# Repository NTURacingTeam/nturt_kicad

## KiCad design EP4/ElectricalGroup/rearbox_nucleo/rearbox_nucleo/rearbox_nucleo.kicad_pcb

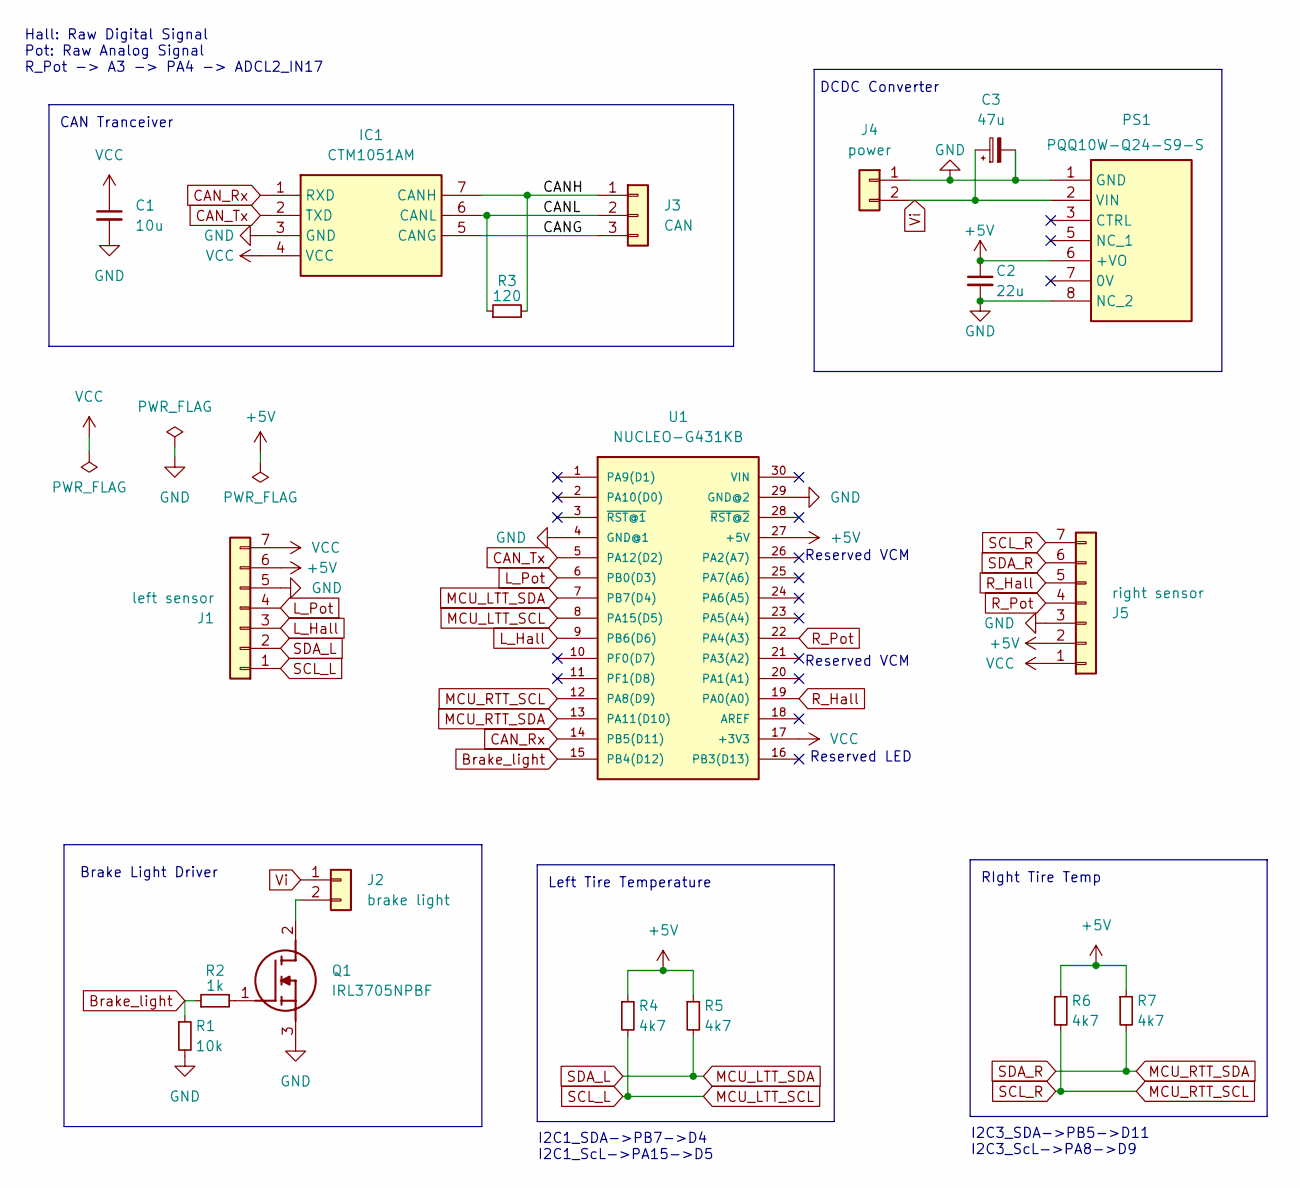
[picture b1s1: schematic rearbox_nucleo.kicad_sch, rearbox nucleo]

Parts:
C1: 10u; C_0805_2012Metric_Pad1.18x1.45mm_HandSolder
C2: 22u; CP_Radial_D6.3mm_P2.50mm
C3: 47u; CP_Radial_Tantal_D6.0mm_P2.50mm
IC1: CTM1051AM; Manufacturer_Part_Number CTM1051AM
J1: left sensor; JST_XH_B7B-XH-A_1x07_P2.50mm_Vertical
J2: brake light; JST_XH_B2B-XH-A_1x02_P2.50mm_Vertical
J3: CAN; JST_XH_B3B-XH-A_1x03_P2.50mm_Vertical
J4: power; JST_XH_B2B-XH-A_1x02_P2.50mm_Vertical
J5: right sensor; JST_XH_B7B-XH-A_1x07_P2.50mm_Vertical
PS1: PQQ10W-Q24-S9-S; PQQ10WQ24S9S; Manufacturer_Part_Number PQQ10W-Q24-S9-S
Q1: IRL3705NPBF; TO254P469X1042X1930-3P; Manufacturer_Part_Number IRL3705NPBF; Mouser Part Number 942-IRL3705NPBF
R1: 10k; R_0603_1608Metric_Pad0.98x0.95mm_HandSolder
R2: 1k; R_0603_1608Metric_Pad0.98x0.95mm_HandSolder
R3: 120; R_1206_3216Metric_Pad1.30x1.75mm_HandSolder
R4, R5, R6, R7: 4k7; R_0603_1608Metric_Pad0.98x0.95mm_HandSolder
U1: NUCLEO-G431KB; MANUFACTURER_PART_NUMBER NUCLEO-F303K8

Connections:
+5V: C2.1, J1.6, J5.2, PS1.6 (+VO), R4.1, R5.1, R6.1, R7.1, U1.27 (+5V)
/CANG: IC1.5 (CANG), J3.3
/CANH: IC1.7 (CANH), J3.1, R3.2
/CANL: IC1.6 (CANL), J3.2, R3.1
Brake_light: R1.1, R2.1, U1.15 (PB4(D12))
CAN_Rx: IC1.1 (RXD), U1.14 (PB5(D11))
CAN_Tx: IC1.2 (TXD), U1.5 (PA12(D2))
GND: C1.2, C2.2, C3.2, IC1.3 (GND), J1.5, J4.1, J5.3, PS1.1 (GND), PS1.8 (NC_2), Q1.3 (S), R1.2, U1.4 (GND@1), U1.29 (GND@2)
L_Hall: J1.3, U1.9 (PB6(D6))
L_Pot: J1.4, U1.6 (PB0(D3))
MCU_LTT_SCL: J1.1, R4.2, U1.8 (PA15(D5))
MCU_LTT_SDA: J1.2, R5.2, U1.7 (PB7(D4))
MCU_RTT_SCL: J5.7, R6.2, U1.12 (PA8(D9))
MCU_RTT_SDA: J5.6, R7.2, U1.13 (PA11(D10))
unnamed: J2.2, Q1.2 (D)
unnamed: Q1.1 (G), R2.2
R_Hall: J5.5, U1.19 (PA0(A0))
R_Pot: J5.4, U1.22 (PA4(A3))
VCC: C1.1, IC1.4 (VCC), J1.7, J5.1, U1.17 (+3V3)
Vi: C3.1, J2.1, J4.2, PS1.2 (VIN)

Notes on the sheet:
RIght Tire Temp
Brake Light Driver
I2C3_SDA->PB5->D11 I2C3_ScL->PA8->D9
Reserved VCM
Reserved LED
Left Tire Temperature
I2C1_SDA->PB7->D4 I2C1_ScL->PA15->D5
CAN Tranceiver
Hall: Raw Digital Signal Pot: Raw Analog Signal R_Pot -> A3 -> PA4 -> ADCL2_IN17
DCDC Converter

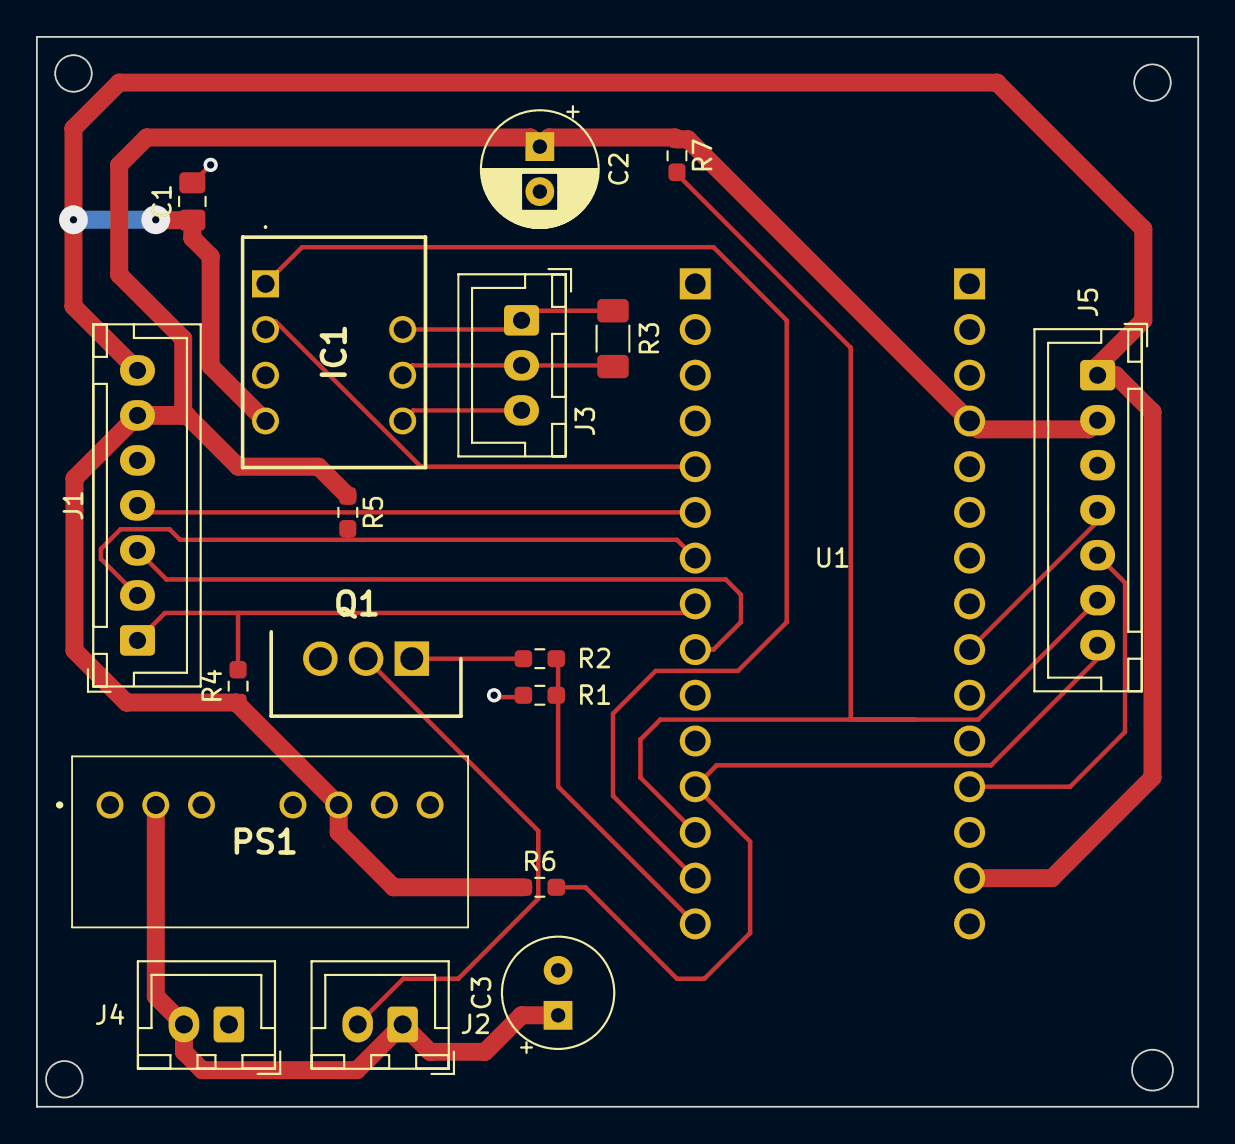
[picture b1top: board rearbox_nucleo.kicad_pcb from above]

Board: 2 copper layers, 64.5 x 59.4 mm, 19 parts (0 on the bottom side), 20 nets.

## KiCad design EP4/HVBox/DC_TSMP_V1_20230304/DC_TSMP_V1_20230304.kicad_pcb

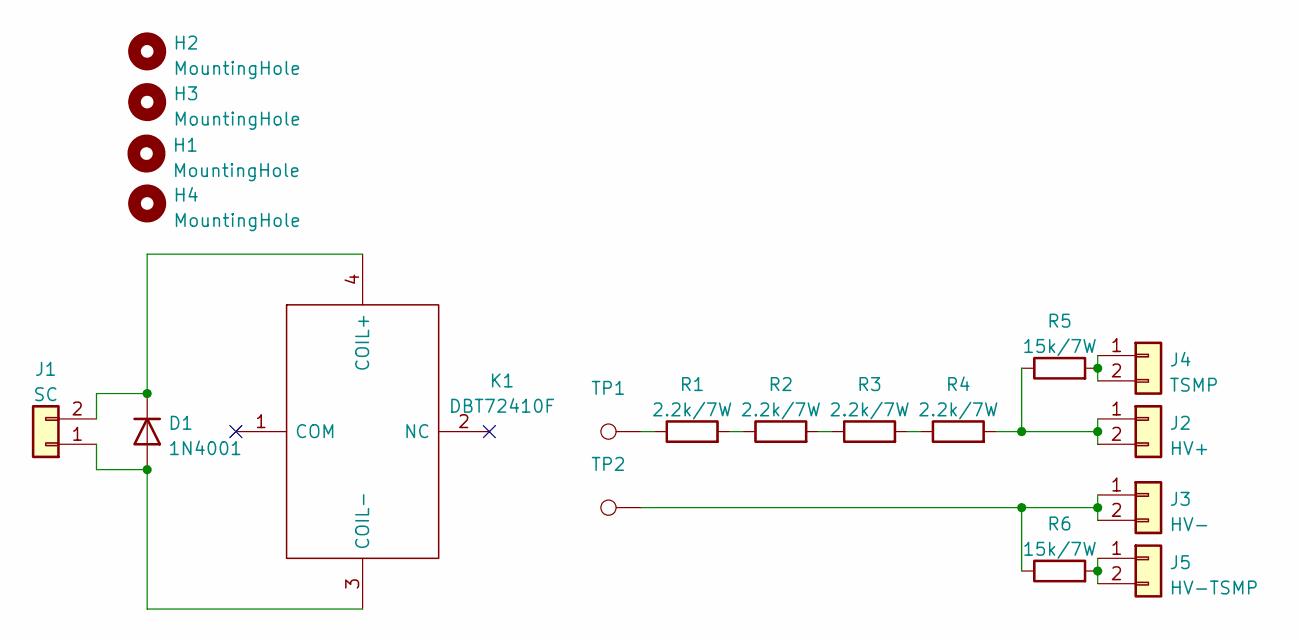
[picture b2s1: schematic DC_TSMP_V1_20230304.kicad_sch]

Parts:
D1: 1N4001; D_DO-41_SOD81_P10.16mm_Horizontal
H1, H2, H3, H4: MountingHole; MountingHole_4.3mm_M4
J1: SC; JST_PH_B2B-PH-K_1x02_P2.00mm_Vertical
J2: HV+; DF33C2P33DSA24
J3: HV-; DF33C2P33DSA24
J4: TSMP; DF33C2P33DSA24
J5: HV-TSMP; DF33C2P33DSA24
K1: DBT72410F; DBT72410; Manufacturer_Part_Number DBT72410
R1, R2, R3, R4: 2.2k/7W; RESM24595X990N
R5, R6: 15k/7W; RESM24595X990N
TP1, TP2: TestPoint_Loop_D2.50mm_Drill1.0mm

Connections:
unnamed: D1.1 (K), J1.2, K1.4 (COIL+)
unnamed: D1.2 (A), J1.1, K1.3 (COIL-)
unnamed: J2.1, J2.2, R4.2, R5.1
unnamed: J3.1, J3.2, R6.1, TP2.1
unnamed: J4.1, J4.2, R5.2
unnamed: J5.1, J5.2, R6.2
unnamed: R1.1, TP1.1
unnamed: R1.2, R2.1
unnamed: R2.2, R3.1
unnamed: R3.2, R4.1

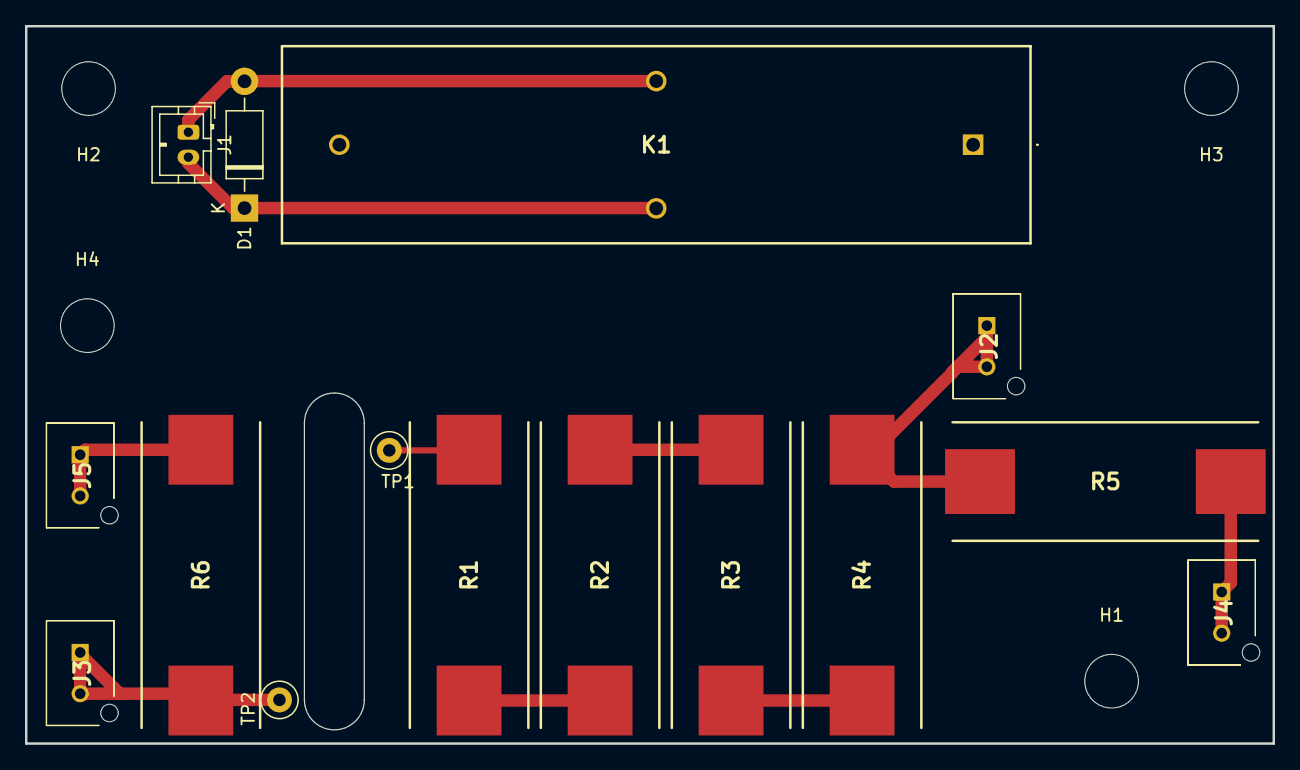
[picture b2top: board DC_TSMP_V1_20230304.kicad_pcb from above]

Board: 2 copper layers, 100.0 x 57.5 mm, 19 parts (0 on the bottom side), 10 nets.

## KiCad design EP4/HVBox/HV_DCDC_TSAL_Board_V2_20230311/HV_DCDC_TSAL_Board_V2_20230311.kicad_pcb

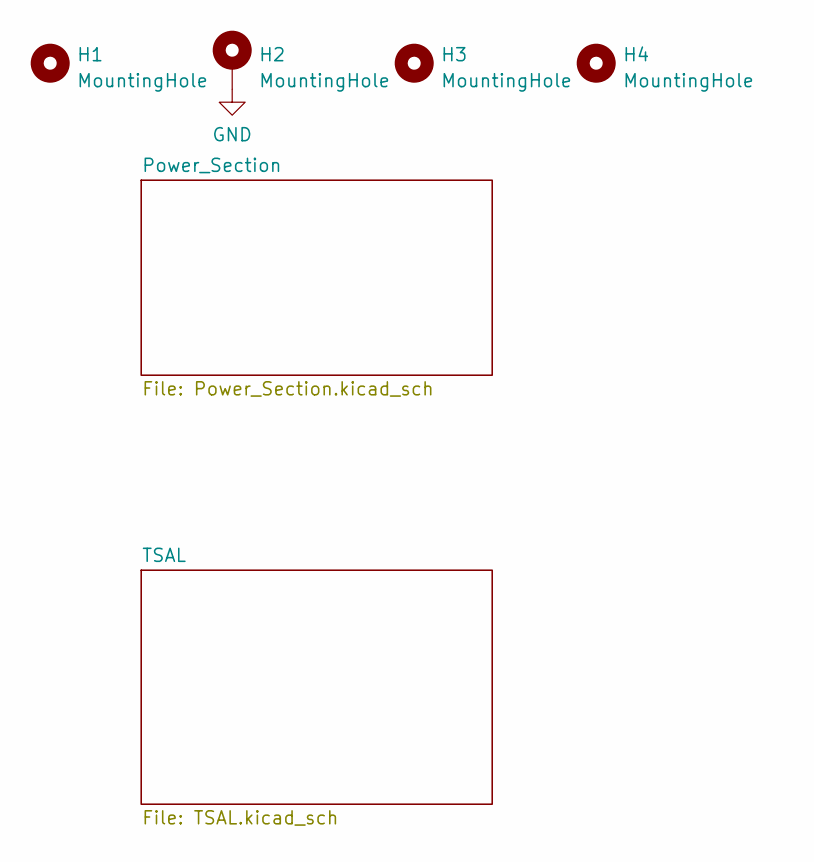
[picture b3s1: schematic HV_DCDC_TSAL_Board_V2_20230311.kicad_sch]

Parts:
H1, H3, H4: MountingHole; MountingHole_4.3mm_M4
H2: MountingHole; MountingHole_4.3mm_M4_Pad_Via

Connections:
GND: H2.1; also elsewhere on the board

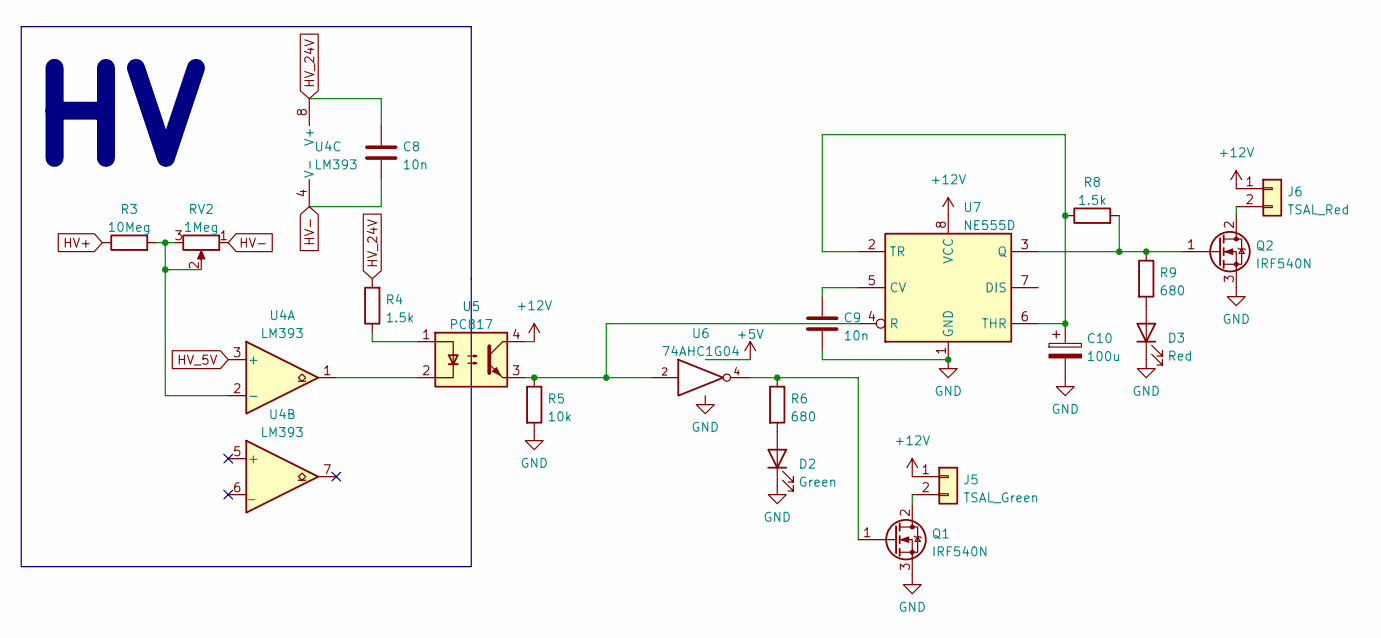
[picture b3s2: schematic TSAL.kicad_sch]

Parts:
C8: 10n; C_Disc_D4.7mm_W2.5mm_P5.00mm
C9: 10n; C_1206_3216Metric_Pad1.33x1.80mm_HandSolder
C10: 100u; C_1206_3216Metric_Pad1.33x1.80mm_HandSolder
D2: Green; D_1206_3216Metric_Pad1.42x1.75mm_HandSolder
D3: Red; D_1206_3216Metric_Pad1.42x1.75mm_HandSolder
J5: TSAL_Green; JST_PH_B2B-PH-K_1x02_P2.00mm_Vertical
J6: TSAL_Red; JST_PH_B2B-PH-K_1x02_P2.00mm_Vertical
Q1, Q2: IRF540N; TO-220-3_Vertical
R3: 10Meg; R_Axial_DIN0309_L9.0mm_D3.2mm_P15.24mm_Horizontal
R4: 1.5k; R_Axial_DIN0309_L9.0mm_D3.2mm_P12.70mm_Horizontal
R5: 10k; R_1206_3216Metric_Pad1.30x1.75mm_HandSolder
R6, R9: 680; R_1206_3216Metric_Pad1.30x1.75mm_HandSolder
R8: 1.5k; R_1206_3216Metric_Pad1.30x1.75mm_HandSolder
RV2: 1Meg; Potentiometer_Vishay_T73YP_Vertical
U4: LM393; DIP-8_W10.16mm
U5: PC817; DIP-4_W7.62mm
U6: 74AHC1G04; SOT-353_SC-70-5_Handsoldering
U7: NE555D; SOIC-8_3.9x4.9mm_P1.27mm

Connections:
+5V: U6.5 (VCC); also elsewhere on the board
+12V: J5.1, J6.1, U5.4, U7.8 (VCC); also elsewhere on the board
GND: C9.2, C10.2, D2.1 (K), D3.1 (K), Q1.3 (S), Q2.3 (S), R5.2, U6.3 (GND), U7.1 (GND); also elsewhere on the board
HV+: R3.1; also elsewhere on the board
HV-: C8.2, RV2.1, U4.4 (V-); also elsewhere on the board
HV_5V: U4.3 (+); also elsewhere on the board
HV_24V: C8.1, R4.2, U4.8 (V+); also elsewhere on the board
unnamed: C9.1, U7.5 (CV)
unnamed: C10.1, R8.1, U7.2 (TR), U7.6 (THR)
unnamed: D2.2 (A), R6.2
unnamed: D3.2 (A), R9.2
unnamed: J5.2, Q1.2 (D)
unnamed: J6.2, Q2.2 (D)
unnamed: Q1.1 (G), R6.1, U6.4
unnamed: Q2.1 (G), R8.2, R9.1, U7.3 (Q)
unnamed: R3.2, RV2.2, RV2.3, U4.2 (-)
unnamed: R4.1, U5.1
unnamed: R5.1, U5.3, U6.2, U7.4 (R)
unnamed: U4.1, U5.2

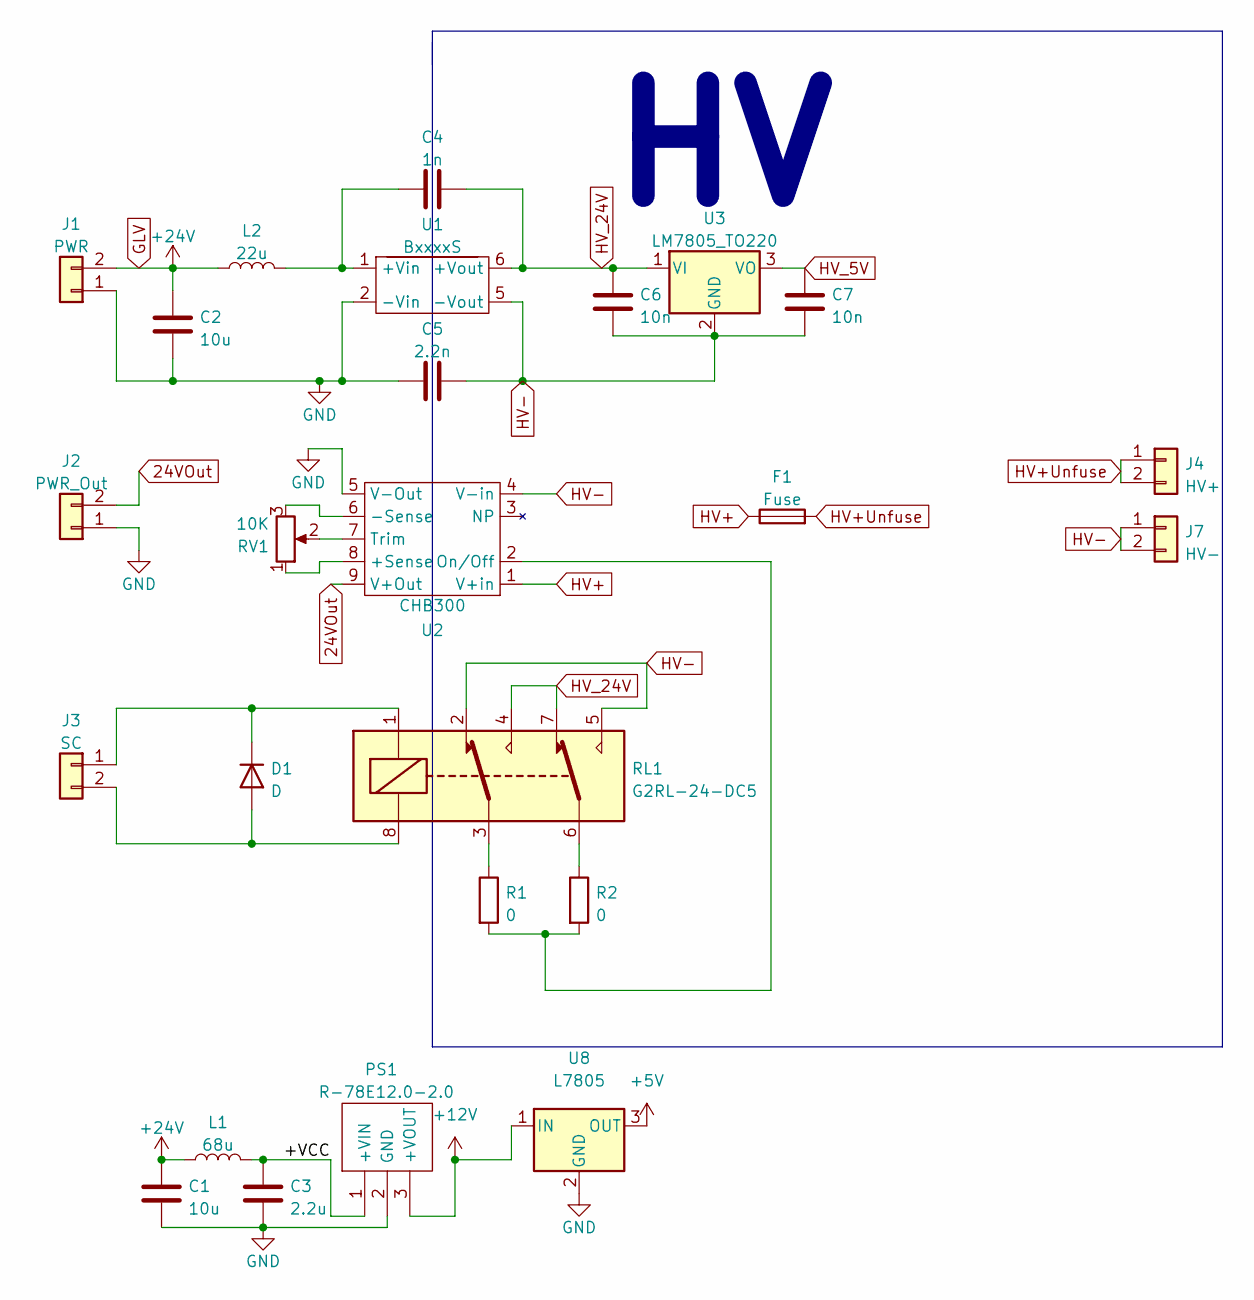
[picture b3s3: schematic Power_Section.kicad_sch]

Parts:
C1, C2: 10u; C_1206_3216Metric_Pad1.33x1.80mm_HandSolder
C3: 2.2u; C_1206_3216Metric_Pad1.33x1.80mm_HandSolder
C4: 1n; C_Axial_L5.1mm_D3.1mm_P15.00mm_Horizontal
C5: 2.2n; C_Axial_L5.1mm_D3.1mm_P15.00mm_Horizontal
C6, C7: 10n; C_Disc_D4.7mm_W2.5mm_P5.00mm
D1: D; D_DO-41_SOD81_P10.16mm_Horizontal
F1: Fuse; 65600001009
J1: PWR; JST_PH_B2B-PH-K_1x02_P2.00mm_Vertical
J2: PWR_Out; DF63M2P396DSA01
J3: SC; JST_PH_B2B-PH-K_1x02_P2.00mm_Vertical
J4: HV+; DF33C2P33DSA24
J7: HV-; DF33C2P33DSA24
L1: 68u; RLS686
L2: 22u; RLS226R
PS1: R-78E12.0-2.0; R78E5010; Mouser Part Number 919-R-78E5.0-1.0
R1, R2: 0; R_Axial_DIN0309_L9.0mm_D3.2mm_P12.70mm_Horizontal
RL1: G2RL-24-DC5; Relay_DPDT_Omron_G2RL
RV1: 10K; Potentiometer_Vishay_T73YP_Vertical
U1: BxxxxS; RB2424S
U2: CHB300; CHB300W48S12
U3: LM7805_TO220; TO-220-3_Vertical
U8: L7805; TO-220-3_Vertical

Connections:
24VOut: J2.2, U2.9 (V+Out)
+5V: U8.3 (OUT); also elsewhere on the board
+12V: PS1.3 (+VOUT), U8.1 (IN); also elsewhere on the board
/Power_Section/+VCC: C3.1, L1.2, PS1.1 (+VIN)
GLV: C1.1, C2.1, J1.2, L1.1, L2.1
GND: C1.2, C2.2, C3.2, C5.1, J1.1, J2.1, PS1.2 (GND), U1.2 (-Vin), U2.5 (V-Out), U8.2 (GND); also elsewhere on the board
HV+: F1.1, U2.1 (V+in); also elsewhere on the board
HV+Unfuse: F1.2, J4.1, J4.2
HV-: C5.2, C6.2, C7.2, J7.1, J7.2, RL1.2, RL1.5, U1.5 (-Vout), U2.4 (V-in), U3.2 (GND); also elsewhere on the board
HV_5V: C7.1, U3.3 (VO); also elsewhere on the board
HV_24V: C4.2, C6.1, RL1.4, RL1.7, U1.6 (+Vout), U3.1 (VI); also elsewhere on the board
unnamed: C4.1, L2.2, U1.1 (+Vin)
unnamed: D1.1 (K), J3.1, RL1.1
unnamed: D1.2 (A), J3.2, RL1.8
unnamed: R1.1, RL1.3
unnamed: R1.2, R2.2, U2.2 (On/Off)
unnamed: R2.1, RL1.6
unnamed: RV1.1, U2.8 (+Sense)
unnamed: RV1.2, U2.7 (Trim)
unnamed: RV1.3, U2.6 (-Sense)

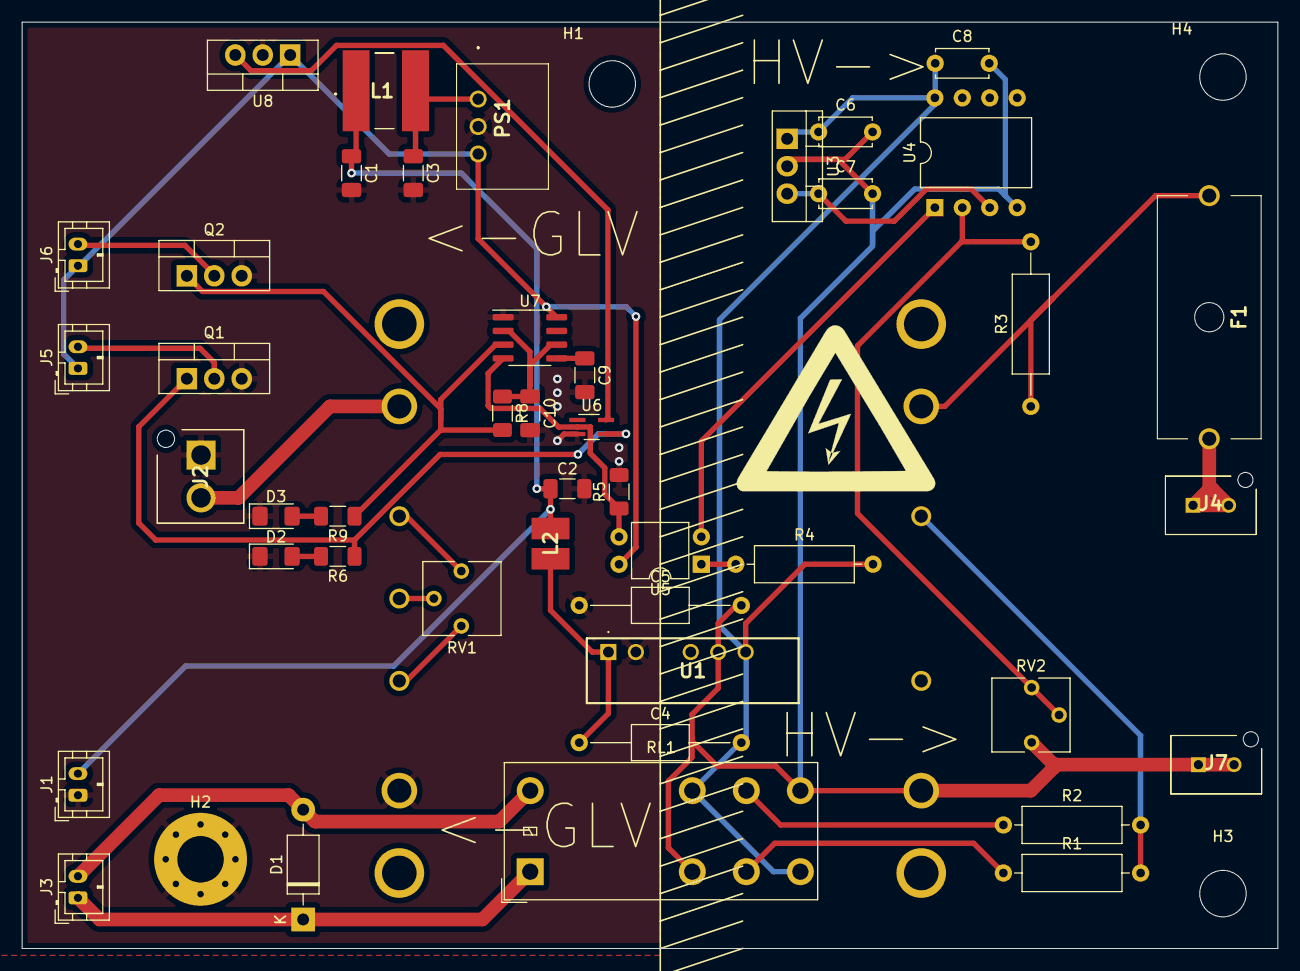
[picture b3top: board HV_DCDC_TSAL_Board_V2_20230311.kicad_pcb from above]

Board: 2 copper layers, 116.2 x 85.7 mm, 49 parts (1 on the bottom side), 32 nets.

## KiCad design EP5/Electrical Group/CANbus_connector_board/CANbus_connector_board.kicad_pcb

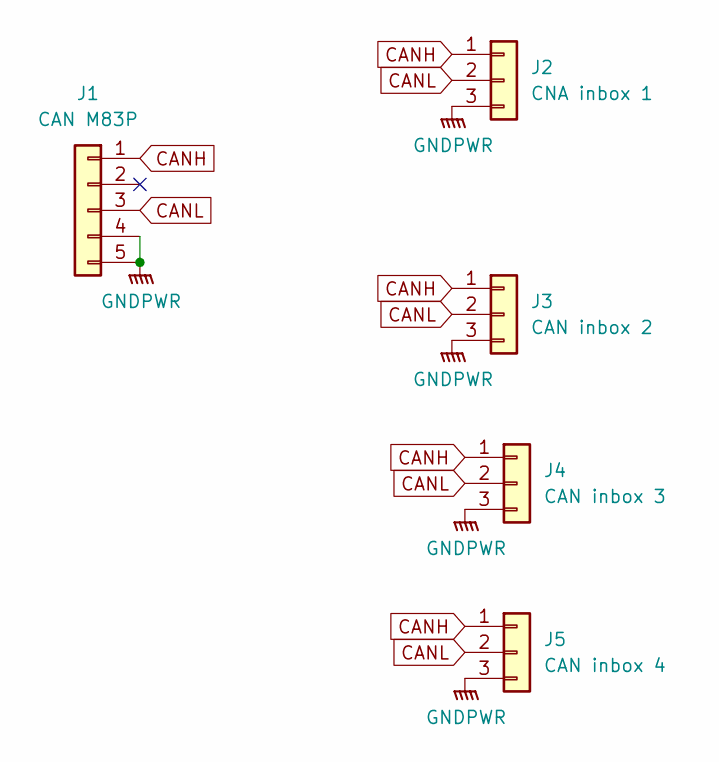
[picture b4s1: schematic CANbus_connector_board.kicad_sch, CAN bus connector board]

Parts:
J1: CAN M83P; WP-03F3-09-11
J2: CNA inbox 1; JST_XH_S3B-XH-A_1x03_P2.50mm_Horizontal
J3: CAN inbox 2; JST_XH_S3B-XH-A_1x03_P2.50mm_Horizontal
J4: CAN inbox 3; JST_XH_S3B-XH-A_1x03_P2.50mm_Horizontal
J5: CAN inbox 4; JST_XH_S3B-XH-A_1x03_P2.50mm_Horizontal

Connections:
CANH: J1.1, J2.1, J3.1, J4.1, J5.1
CANL: J1.3, J2.2, J3.2, J4.2, J5.2
GNDPWR: J1.4, J1.5, J2.3, J3.3, J4.3, J5.3

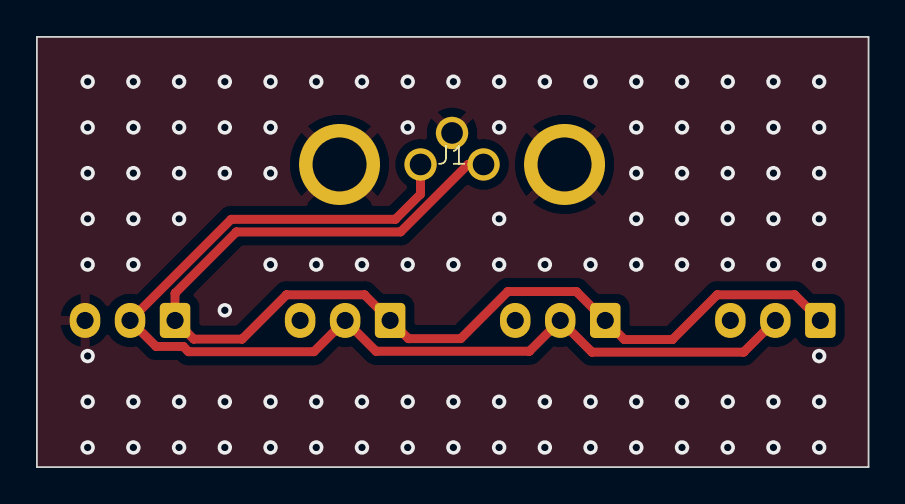
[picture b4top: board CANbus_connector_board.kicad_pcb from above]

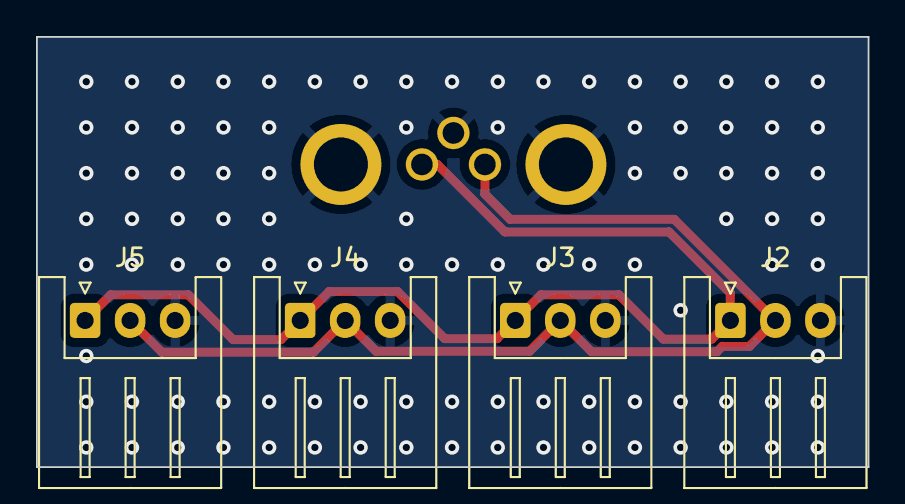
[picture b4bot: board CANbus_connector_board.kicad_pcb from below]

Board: 2 copper layers, 46.2 x 23.9 mm, 5 parts (4 on the bottom side), 3 nets.

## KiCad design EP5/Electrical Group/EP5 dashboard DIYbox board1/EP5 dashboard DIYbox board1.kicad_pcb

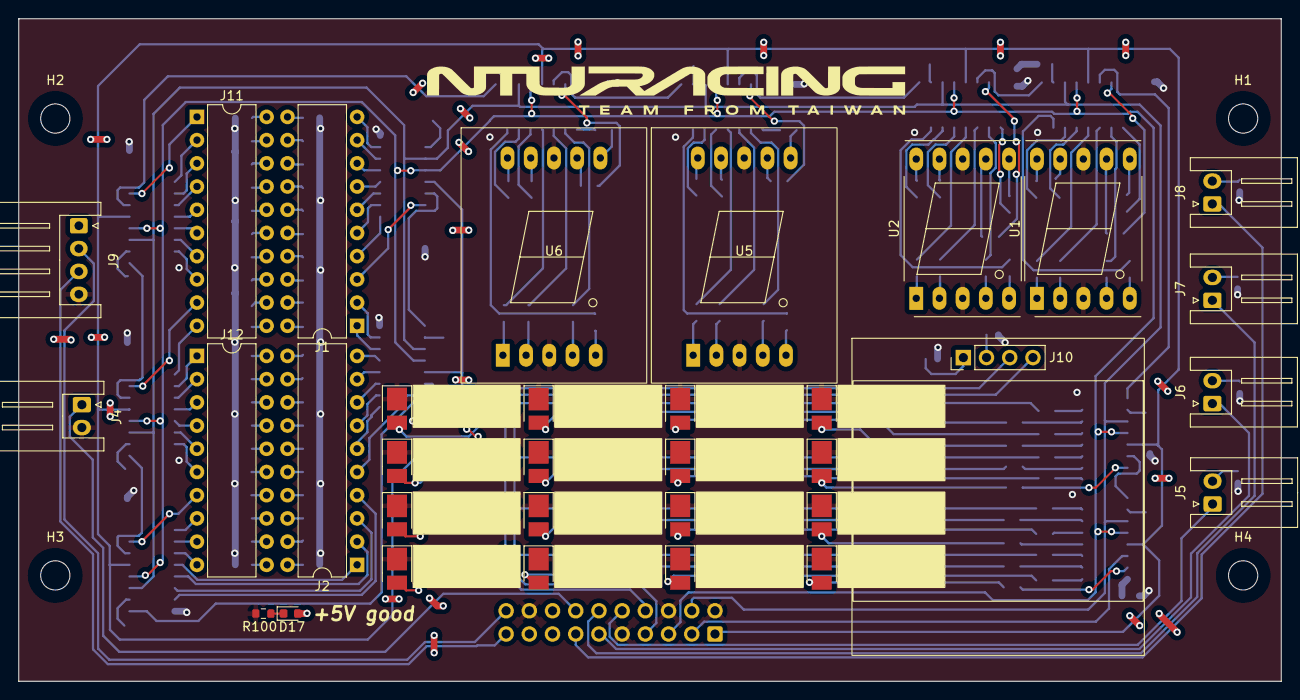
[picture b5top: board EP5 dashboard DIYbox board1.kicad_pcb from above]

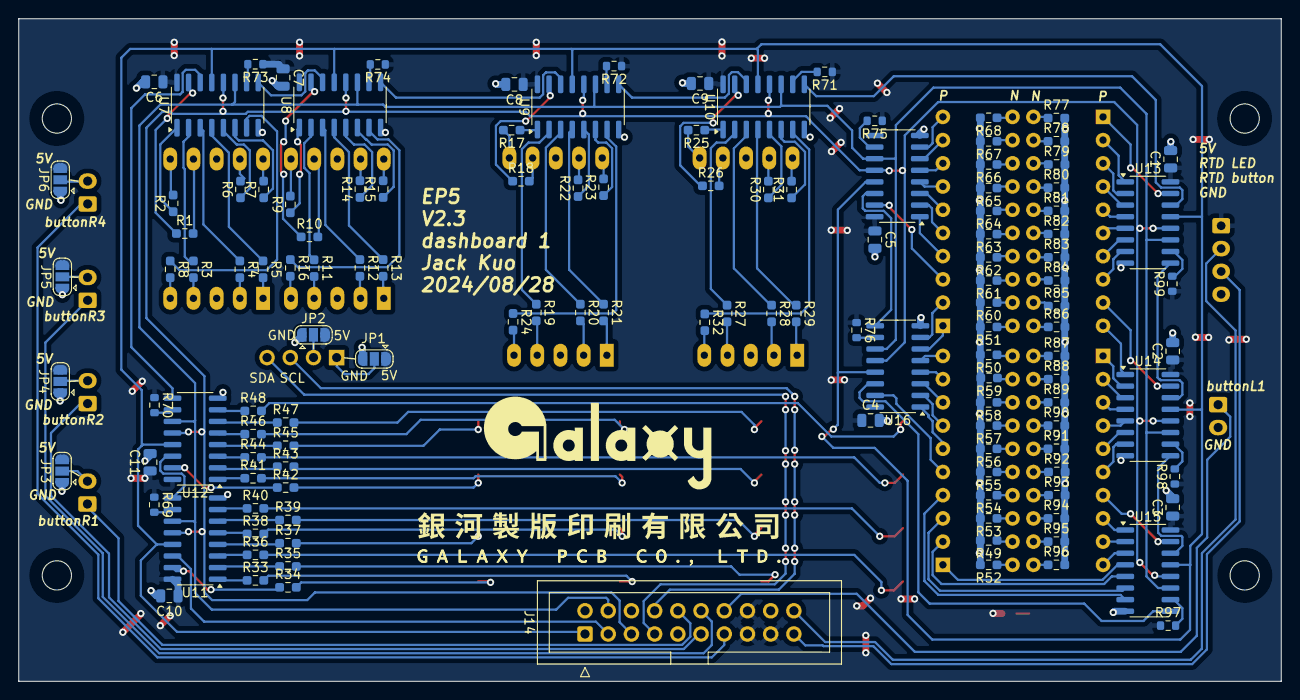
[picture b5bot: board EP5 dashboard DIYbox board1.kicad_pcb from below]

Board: 2 copper layers, 138.2 x 72.5 mm, 165 parts (128 on the bottom side), 219 nets.

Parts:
C1, C2, C3, C4, C5, C6, C7, C8, C9, C10, C11: 0u1; C_0805_2012Metric
D1, D2, D3, D4, D5, D6, D7, D8, D9, D10, D11, D12, D13, D14, D15, D16: LED; LED_PLCC_2835_Handsoldering
D17: White 5VGood; LED_0603_1608Metric
H1, H2, H3, H4: MountingHole_Pad; MountingHole_3.2mm_M3
J1: pedal2-2 GREEN; DIP-20_W7.62mm
J2: pedal2-1 GREEN; DIP-20_W7.62mm
J4: R1; JST_XH_S2B-XH-A_1x02_P2.50mm_Horizontal
J5: L1; JST_XH_S2B-XH-A_1x02_P2.50mm_Horizontal
J6: L2; JST_XH_S2B-XH-A_1x02_P2.50mm_Horizontal
J7: L3; JST_XH_S2B-XH-A_1x02_P2.50mm_Horizontal
J8: L4; JST_XH_S2B-XH-A_1x02_P2.50mm_Horizontal
J9: RTD; JST_XH_S4B-XH-A_1x04_P2.50mm_Horizontal
J10: 12864; 12864_1.3_I2C
J11: pedal1-1 RED; DIP-20_W7.62mm
J12: pedal1-2 RED; DIP-20_W7.62mm
J14: screen; IDC-Header_2x10_P2.54mm_Vertical
JP1, JP3, JP4, JP5, JP6: OLED_P1; SolderJumper-3_P1.3mm_Open_RoundedPad1.0x1.5mm
JP2: OLED_P2; SolderJumper-3_P1.3mm_Open_RoundedPad1.0x1.5mm
R1, R2, R3, R4, R5, R6, R7, R8, R9, R10, R11, R12, R13, R14, R15, R16: 390R; R_0603_1608Metric_Pad0.98x0.95mm_HandSolder
R17, R18, R19, R20, R21, R22, R23, R24, R25, R26, R27, R28, R29, R30, R31, R32: 180R; R_0603_1608Metric_Pad0.98x0.95mm_HandSolder
R33, R34, R35, R36, R37, R38, R39, R40, R41, R42, R43, R44, R45, R46, R47, R48, R77, R78, R79, R80, R81, R82, R83, R84, R85, R86, R87, R88, R89, R90, R91, R92, R93, R94, R95, R96: 220R; R_0603_1608Metric_Pad0.98x0.95mm_HandSolder
R49, R50, R51, R52, R53, R54, R55, R56, R57, R58, R59, R60, R61, R62, R63, R64, R65, R66, R67, R68: 330R; R_0603_1608Metric_Pad0.98x0.95mm_HandSolder
R69, R70, R71, R72, R73, R74, R75, R76, R97, R98, R99: 10k; R_0603_1608Metric
R100: 510R; R_0603_1608Metric
U1: Seg1 GREEN .56; 7SegmentLED_LTS6760_LTS6780
U2: Seg2 GREEN .56; 7SegmentLED_LTS6760_LTS6780
U5: Seg3 BLUE .8; 7SEGMENT-08inch
U6: Seg4 BLUE .8; 7SEGMENT-08inch
U7, U8, U9, U10, U11, U12, U13, U14, U15, U16, U17: 74HC595; SOIC-16_3.9x9.9mm_P1.27mm

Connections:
+5V: C1.1, C2.1, C3.1, C4.1, C5.1, C6.1, C7.1, C8.1, C9.1, C10.1, C11.1, D17.2 (A), J9.1, J14.15, J14.16, J14.17, JP1.1 (A), JP2.3 (B), JP3.3 (B), JP4.3 (B), JP5.3 (B), JP6.3 (B), R69.1, R70.1, R71.1, R72.1, R73.1, R74.1, R75.1, R76.1, R97.1, R98.1, R99.1, U7.16 (VCC), U8.16 (VCC), U9.16 (VCC), U10.16 (VCC), U11.16 (VCC), U12.16 (VCC), U13.16 (VCC), U14.16 (VCC), U15.16 (VCC), U16.16 (VCC), U17.16 (VCC)
ButtonL1_raw: J4.1, J14.14
ButtonR1_raw: J5.1, J14.10
ButtonR2_raw: J6.1, J14.11
ButtonR3_raw: J7.1, J14.12
ButtonR4_raw: J8.1, J14.13
ButtonRTD_raw: J9.3, J14.19
ButtonRTDlight: J9.2, J14.20
GND: C1.2, C2.2, C3.2, C4.2, C5.2, C6.2, C7.2, C8.2, C9.2, C10.2, C11.2, D1.1 (K), D2.1 (K), D3.1 (K), D4.1 (K), D5.1 (K), D6.1 (K), D7.1 (K), D8.1 (K), D9.1 (K), D10.1 (K), D11.1 (K), D12.1 (K), D13.1 (K), D14.1 (K), D15.1 (K), D16.1 (K), J4.2, J9.4, J14.2, J14.6, J14.9, J14.18, JP1.3 (B), JP2.1 (A), JP3.1 (A), JP4.1 (A), JP5.1 (A), JP6.1 (A), R49.2, R50.2, R51.2, R52.2, R53.2, R54.2, R55.2, R56.2, R57.2, R58.2, R59.2, R60.2, R61.2, R62.2, R63.2, R64.2, R65.2, R66.2, R67.2, R68.2, R77.2, R78.2, R79.2, R80.2, R81.2, R82.2, R83.2, R84.2, R85.2, R86.2, R87.2, R88.2, R89.2, R90.2, R91.2, R92.2, R93.2, R94.2, R95.2, R96.2, R100.2, U1.3 (CC), U1.8 (CC), U2.3 (CC), U2.8 (CC), U5.3 (CC), U5.8 (CC), U6.3 (CC), U6.8 (CC), U7.8 (GND), U8.8 (GND), U9.8 (GND), U10.8 (GND), U11.8 (GND), U12.8 (GND), U13.8 (GND), U14.8 (GND), U15.8 (GND), U16.8 (GND), U17.8 (GND)
LEDend1: U13.9 (QH'), U14.14 (SER)
LEDend2: U14.9 (QH'), U15.14 (SER)
LEDend3: U15.9 (QH'), U16.14 (SER)
LEDend4: U16.9 (QH'), U17.14 (SER)
unnamed: D1.2 (A), R34.2
unnamed: D2.2 (A), R33.2
unnamed: D3.2 (A), R35.2
unnamed: D4.2 (A), R36.2
unnamed: D5.2 (A), R37.2
unnamed: D6.2 (A), R38.2
unnamed: D7.2 (A), R39.2
unnamed: D8.2 (A), R40.2
unnamed: D9.2 (A), R42.2
unnamed: D10.2 (A), R41.2
unnamed: D11.2 (A), R43.2
unnamed: D12.2 (A), R44.2
unnamed: D13.2 (A), R45.2
unnamed: D14.2 (A), R46.2
unnamed: D15.2 (A), R47.2
unnamed: D16.2 (A), R48.2
unnamed: D17.1 (K), R100.1
unnamed: J1.1, U16.6 (QG)
unnamed: J1.2, U16.7 (QH)
unnamed: J1.3, U17.15 (QA)
unnamed: J1.4, U17.1 (QB)
unnamed: J1.5, U17.2 (QC)
unnamed: J1.6, U17.3 (QD)
unnamed: J1.7, U17.4 (QE)
unnamed: J1.8, U17.5 (QF)
unnamed: J1.9, U17.6 (QG)
unnamed: J1.10, U17.7 (QH)
unnamed: J1.11, R68.1
unnamed: J1.12, R67.1
unnamed: J1.13, R66.1
unnamed: J1.14, R65.1
unnamed: J1.15, R64.1
unnamed: J1.16, R63.1
unnamed: J1.17, R62.1
unnamed: J1.18, R61.1
unnamed: J1.19, R60.1
unnamed: J1.20, R51.1
unnamed: J2.1, U15.4 (QE)
unnamed: J2.2, U15.5 (QF)
unnamed: J2.3, U15.6 (QG)
unnamed: J2.4, U15.7 (QH)
unnamed: J2.5, U16.15 (QA)
unnamed: J2.6, U16.1 (QB)
unnamed: J2.7, U16.2 (QC)
unnamed: J2.8, U16.3 (QD)
unnamed: J2.9, U16.4 (QE)
unnamed: J2.10, U16.5 (QF)
unnamed: J2.11, R50.1
unnamed: J2.12, R59.1
unnamed: J2.13, R58.1
unnamed: J2.14, R57.1
unnamed: J2.15, R56.1
unnamed: J2.16, R55.1
unnamed: J2.17, R54.1
unnamed: J2.18, R53.1
unnamed: J2.19, R49.1
unnamed: J2.20, R52.1
unnamed: J5.2, JP3.2 (C)
unnamed: J6.2, JP4.2 (C)
unnamed: J7.2, JP5.2 (C)
unnamed: J8.2, JP6.2 (C)
unnamed: J10.1, JP1.2 (C)
unnamed: J10.2, JP2.2 (C)
unnamed: J11.1, U13.15 (QA)
unnamed: J11.2, U13.1 (QB)
unnamed: J11.3, U13.2 (QC)
unnamed: J11.4, U13.3 (QD)
unnamed: J11.5, U13.4 (QE)
unnamed: J11.6, U13.5 (QF)
unnamed: J11.7, U13.6 (QG)
unnamed: J11.8, U13.7 (QH)
unnamed: J11.9, U14.15 (QA)
unnamed: J11.10, U14.1 (QB)
unnamed: J11.11, R86.1
unnamed: J11.12, R85.1
unnamed: J11.13, R84.1
unnamed: J11.14, R83.1
unnamed: J11.15, R82.1
unnamed: J11.16, R81.1
unnamed: J11.17, R80.1
unnamed: J11.18, R79.1
unnamed: J11.19, R78.1
unnamed: J11.20, R77.1
unnamed: J12.1, U14.2 (QC)
unnamed: J12.2, U14.3 (QD)
unnamed: J12.3, U14.4 (QE)
unnamed: J12.4, U14.5 (QF)
unnamed: J12.5, U14.6 (QG)
unnamed: J12.6, U14.7 (QH)
unnamed: J12.7, U15.15 (QA)
unnamed: J12.8, U15.1 (QB)
unnamed: J12.9, U15.2 (QC)
unnamed: J12.10, U15.3 (QD)
unnamed: J12.11, R96.1
unnamed: J12.12, R95.1
unnamed: J12.13, R94.1
unnamed: J12.14, R93.1
unnamed: J12.15, R92.1
unnamed: J12.16, R91.1
unnamed: J12.17, R90.1
unnamed: J12.18, R89.1
unnamed: J12.19, R88.1
unnamed: J12.20, R87.1
unnamed: R1.2, U1.7 (A)
unnamed: R2.2, U1.6 (B)
unnamed: R3.2, U1.4 (C)
unnamed: R4.2, U1.2 (D)
unnamed: R8.2, U1.5 (DP)
unnamed: R5.2, U1.1 (E)
unnamed: R6.2, U1.9 (F)
unnamed: R7.2, U1.10 (G)
unnamed: R10.2, U2.7 (A)
unnamed: R9.2, U2.6 (B)
unnamed: R11.2, U2.4 (C)
unnamed: R12.2, U2.2 (D)
unnamed: R16.2, U2.5 (DP)
unnamed: R13.2, U2.1 (E)
unnamed: R14.2, U2.9 (F)
unnamed: R15.2, U2.10 (G)
unnamed: R18.2, U5.7 (A)
unnamed: R17.2, U5.6 (B)
unnamed: R19.2, U5.4 (C)
unnamed: R20.2, U5.2 (D)
unnamed: R24.2, U5.5 (DP)
unnamed: R21.2, U5.1 (E)
unnamed: R22.2, U5.9 (F)
unnamed: R23.2, U5.10 (G)
unnamed: R26.2, U6.7 (A)
unnamed: R25.2, U6.6 (B)
unnamed: R27.2, U6.4 (C)
unnamed: R28.2, U6.2 (D)
unnamed: R32.2, U6.5 (DP)
unnamed: R29.2, U6.1 (E)
unnamed: R30.2, U6.9 (F)
unnamed: R31.2, U6.10 (G)
unnamed: R1.1, U7.15 (QA)
unnamed: R2.1, U7.1 (QB)
unnamed: R3.1, U7.2 (QC)
unnamed: R4.1, U7.3 (QD)
unnamed: R5.1, U7.4 (QE)
unnamed: R6.1, U7.5 (QF)
unnamed: R7.1, U7.6 (QG)
unnamed: U7.9 (QH'), U8.14 (SER)
unnamed: R8.1, U7.7 (QH)
unnamed: R73.2, U7.10 (~SRCLR)
unnamed: R10.1, U8.15 (QA)
unnamed: R9.1, U8.1 (QB)
unnamed: R11.1, U8.2 (QC)
unnamed: R12.1, U8.3 (QD)
unnamed: R13.1, U8.4 (QE)
unnamed: R14.1, U8.5 (QF)
unnamed: R15.1, U8.6 (QG)
unnamed: R16.1, U8.7 (QH)
unnamed: R74.2, U8.10 (~SRCLR)
unnamed: R18.1, U9.15 (QA)
unnamed: R17.1, U9.1 (QB)
unnamed: R19.1, U9.2 (QC)
unnamed: R20.1, U9.3 (QD)
unnamed: R21.1, U9.4 (QE)
unnamed: R22.1, U9.5 (QF)
unnamed: R23.1, U9.6 (QG)
unnamed: R24.1, U9.7 (QH)
unnamed: R72.2, U9.10 (~SRCLR)
unnamed: R26.1, U10.15 (QA)
unnamed: R25.1, U10.1 (QB)
unnamed: R27.1, U10.2 (QC)
unnamed: R28.1, U10.3 (QD)
unnamed: R29.1, U10.4 (QE)
unnamed: R30.1, U10.5 (QF)
unnamed: R31.1, U10.6 (QG)
unnamed: R32.1, U10.7 (QH)
unnamed: U9.9 (QH'), U10.14 (SER)
unnamed: R71.2, U10.10 (~SRCLR)
unnamed: R34.1, U11.15 (QA)
unnamed: R33.1, U11.1 (QB)
unnamed: R35.1, U11.2 (QC)
unnamed: R36.1, U11.3 (QD)
unnamed: R37.1, U11.4 (QE)
unnamed: R38.1, U11.5 (QF)
unnamed: R39.1, U11.6 (QG)
unnamed: U11.9 (QH'), U12.14 (SER)
unnamed: R40.1, U11.7 (QH)
unnamed: R69.2, U11.10 (~SRCLR)
unnamed: R42.1, U12.15 (QA)
unnamed: R41.1, U12.1 (QB)
unnamed: R43.1, U12.2 (QC)
unnamed: R44.1, U12.3 (QD)
unnamed: R45.1, U12.4 (QE)
unnamed: R46.1, U12.5 (QF)
unnamed: R47.1, U12.6 (QG)
unnamed: R48.1, U12.7 (QH)
unnamed: R70.2, U12.10 (~SRCLR)
unnamed: R99.2, U13.10 (~SRCLR)
unnamed: R98.2, U14.10 (~SRCLR)
unnamed: R97.2, U15.10 (~SRCLR)
unnamed: R76.2, U16.10 (~SRCLR)
unnamed: R75.2, U17.10 (~SRCLR)
OE: J14.1, U7.13 (~OE), U8.13 (~OE), U9.13 (~OE), U10.13 (~OE), U11.13 (~OE), U12.13 (~OE), U13.13 (~OE), U14.13 (~OE), U15.13 (~OE), U16.13 (~OE), U17.13 (~OE)
RCLK: J14.5, U7.12 (RCLK), U8.12 (RCLK), U9.12 (RCLK), U10.12 (RCLK), U11.12 (RCLK), U12.12 (RCLK), U13.12 (RCLK), U14.12 (RCLK), U15.12 (RCLK), U16.12 (RCLK), U17.12 (RCLK)
SCL: J10.3, J14.8
SDA: J10.4, J14.7
SER: J14.3, U11.14 (SER)
SRCLK: J14.4, U7.11 (SRCLK), U8.11 (SRCLK), U9.11 (SRCLK), U10.11 (SRCLK), U11.11 (SRCLK), U12.11 (SRCLK), U13.11 (SRCLK), U14.11 (SRCLK), U15.11 (SRCLK), U16.11 (SRCLK), U17.11 (SRCLK)
Seg2End: U8.9 (QH'), U9.14 (SER)
Seg4End: U10.9 (QH'), U13.14 (SER)
Seg6End: U7.14 (SER), U12.9 (QH')
